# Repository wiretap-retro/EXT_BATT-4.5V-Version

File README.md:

# EXT_BATT 4.5V Version
A battery supply for retro motherboards with an EXT_BATT header.

\

\
^--photo from minuszerodegrees showing EXT_BATT header

## Info
I have quite a few 386 and 486 motherboards that have an EXT_BATT header, but I've removed the rechargable Varta. This PCB project is aimed at using the EXT_BATT header to provide a solution to keep your CMOS settings saved and RTC ticking. The MAX40200 chip provides for "ideal diode" functionality with less than a 43mV drop in voltage. It also prevents a charge circuit from trying to charge the LR44 / 357 type battery if the motherboard happens to have a charge circuit on the EXT_BATT header. (rare occurences). I prefer this board because the batteries are cheap, last a long time, and the EXT_BATT header is usually in an easier spot to get to than where the Varta battery is crammed on most boards. I recommend using Japanese made 357 silver-oxide type batteries in this, as they tend not to corrode, and they last much longer. Check the batteries every few years.

## BOM
* This circuit board, ordered from your fabricator of choice. (JLCPCB, PCBway, OSH Park, etc.)
* Maxim MAX40200AUK+T Ideal Diode
* 3x Renata SMTU357-LF battery holder
* 1x04 2.54mm pitch right angle pin socket, or 1x04 2.54mm pitch straight pin socket, or 1x04 2.54mm male pin headers (see below for mounting orientations)
* 3x LR44 / 357 batteries

## Installation
Plug the completed board into the EXT_BATT header. Several motherboards also use an INTERNAL/EXTERNAL jumper to select between the factory installed battery and the EXT_BATT header.
\
\
Mounting orientations:
* Vertical - this PCB sits about 36mm tall when installed vertically. 
* Horizontal - may be possible depending on your board's EXT_BATT header location/orientation and other nearby components.
* Remote - use pin header extension wires to connect to the EXT_BATT header and put the PCB somewhere else in the case.

## Other
Reference material for retro motherboard batteries: http://minuszerodegrees.net/battery/cmos/vintage_motherboard_batteries.htm
\
This project is open source, feel free to do what you want with it.

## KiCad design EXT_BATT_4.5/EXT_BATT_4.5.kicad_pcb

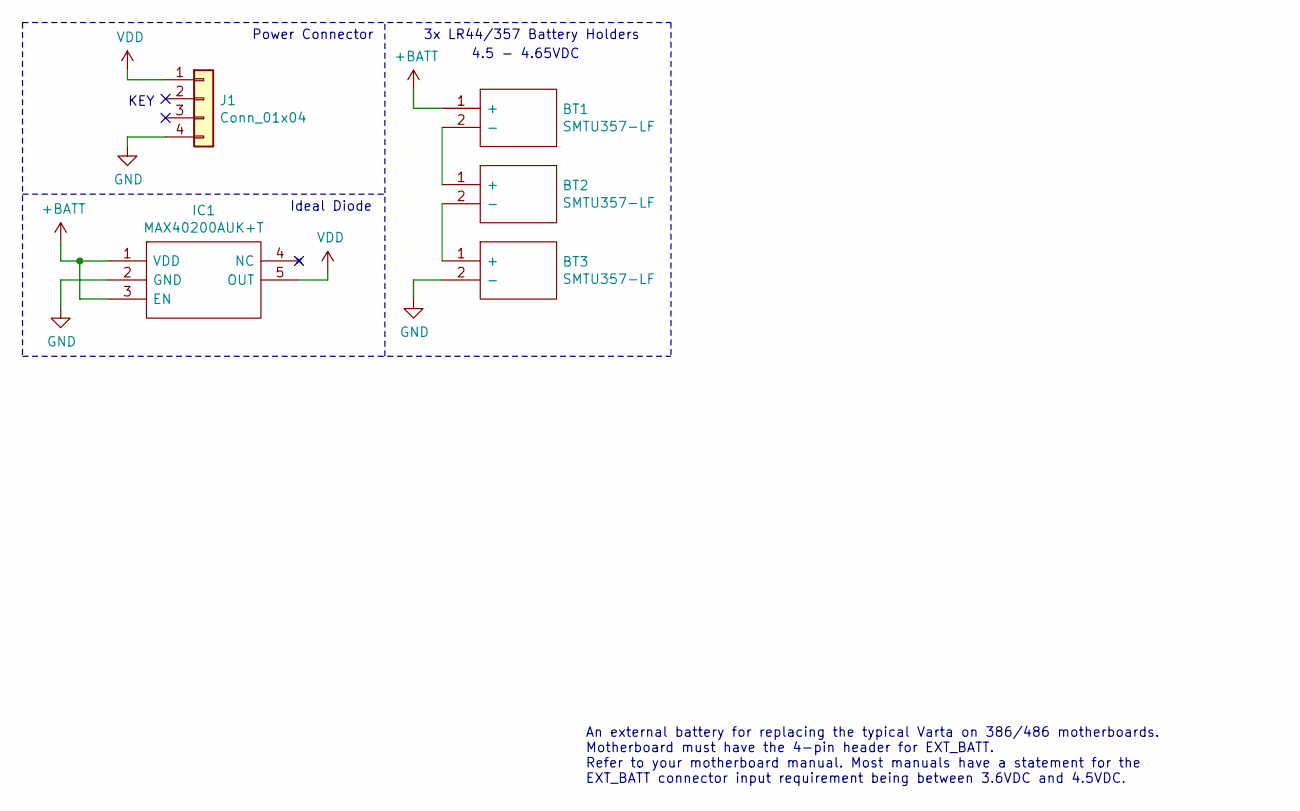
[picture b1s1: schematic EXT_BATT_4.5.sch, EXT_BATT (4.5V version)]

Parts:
BT1, BT2, BT3: SMTU357-LF; SMTU357LF; Mouser Part Number 614-SMTU357-LF
IC1: MAX40200AUK+T; SOT95P280X145-5N; Mouser Part Number 700-MAX40200AUK+T
J1: Conn_01x04; PinSocket_1x04_P2.54mm_Horizontal

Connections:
+BATT: BT1.1 (+), IC1.1 (VDD), IC1.3 (EN)
GND: BT3.2 (-), IC1.2 (GND), J1.4
unnamed: BT1.2 (-), BT2.1 (+)
unnamed: BT2.2 (-), BT3.1 (+)
VDD: IC1.5 (OUT), J1.1

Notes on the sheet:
KEY
3x LR44/357 Battery Holders
4.5 - 4.65VDC
Power Connector
Ideal Diode
An external battery for replacing the typical Varta on 386/486 motherboards. Motherboard must have the 4-pin header for EXT_BATT. Refer to your motherboard manual. Most manuals have a statement for the EXT_BATT connector input requirement being between 3.6VDC and 4.5VDC.

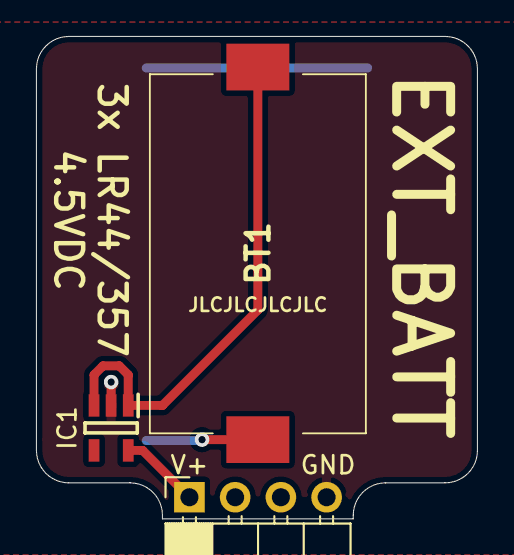
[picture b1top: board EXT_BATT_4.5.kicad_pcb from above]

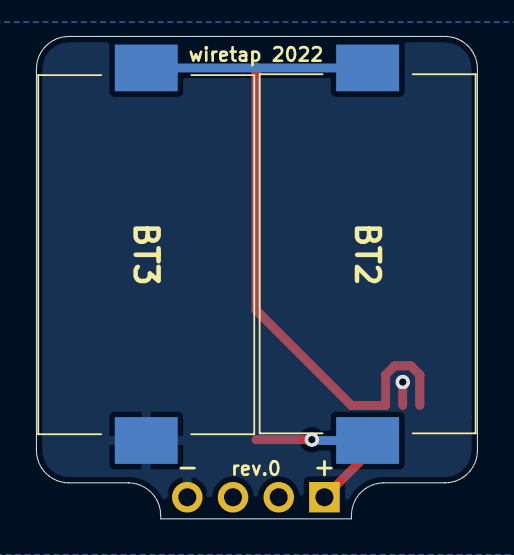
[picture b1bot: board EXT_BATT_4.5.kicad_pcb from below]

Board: 2 copper layers, 24.5 x 26.8 mm, 5 parts (2 on the bottom side), 5 nets.
